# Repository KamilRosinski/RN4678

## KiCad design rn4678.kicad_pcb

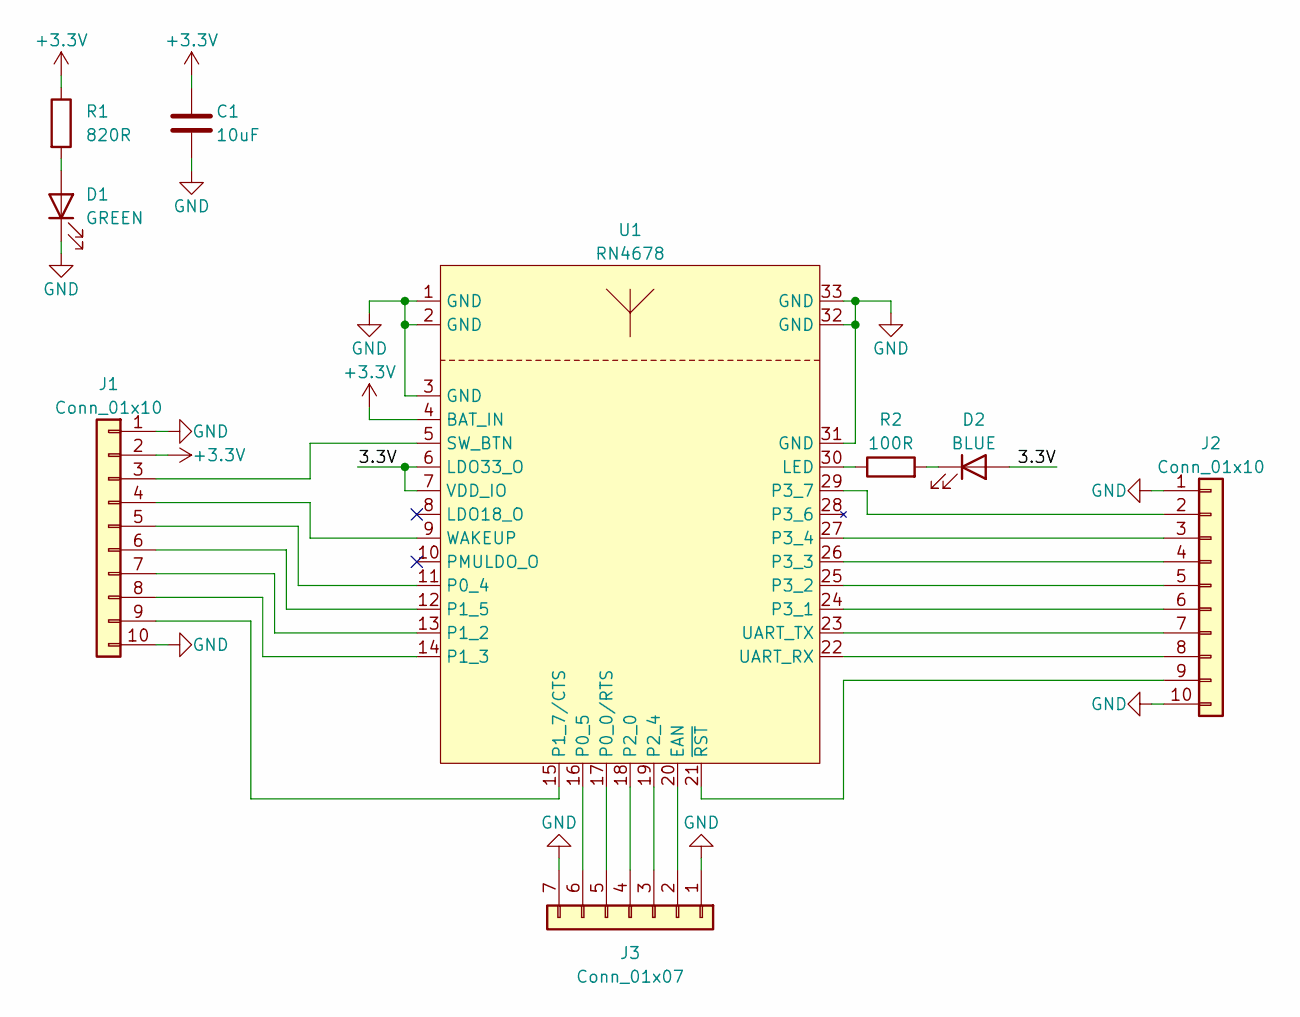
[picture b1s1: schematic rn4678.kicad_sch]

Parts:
C1: 10uF; C_1206_3216Metric
D1: GREEN; LED_0603_1608Metric
D2: BLUE; LED_0603_1608Metric
J1, J2: Conn_01x10; PinHeader_1x10_P2.54mm_Vertical
J3: Conn_01x07; PinHeader_1x07_P2.54mm_Vertical
R1: 820R; R_0603_1608Metric
R2: 100R; R_0603_1608Metric
U1: RN4678

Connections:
+3.3V: C1.1, J1.2, R1.1, U1.4 (BAT_IN)
/3.3V: D2.2 (A), U1.6 (LDO33_O), U1.7 (VDD_IO)
GND: C1.2, D1.1 (K), J1.1, J1.10, J2.1, J2.10, J3.1, J3.7, U1.1 (GND), U1.2 (GND), U1.3 (GND), U1.31 (GND), U1.32 (GND), U1.33 (GND)
unnamed: D1.2 (A), R1.2
unnamed: D2.1 (K), R2.2
unnamed: J1.3, U1.5 (SW_BTN)
unnamed: J1.4, U1.9 (WAKEUP)
unnamed: J1.5, U1.11 (P0_4)
unnamed: J1.6, U1.12 (P1_5)
unnamed: J1.7, U1.13 (P1_2)
unnamed: J1.8, U1.14 (P1_3)
unnamed: J1.9, U1.15 (P1_7/CTS)
unnamed: J2.2, U1.29 (P3_7)
unnamed: J2.3, U1.27 (P3_4)
unnamed: J2.4, U1.26 (P3_3)
unnamed: J2.5, U1.25 (P3_2)
unnamed: J2.6, U1.24 (P3_1)
unnamed: J2.7, U1.23 (UART_TX)
unnamed: J2.8, U1.22 (UART_RX)
unnamed: J2.9, U1.21 (~RST)
unnamed: J3.2, U1.20 (EAN)
unnamed: J3.3, U1.19 (P2_4)
unnamed: J3.4, U1.18 (P2_0)
unnamed: J3.5, U1.17 (P0_0/RTS)
unnamed: J3.6, U1.16 (P0_5)
unnamed: R2.1, U1.30 (LED)

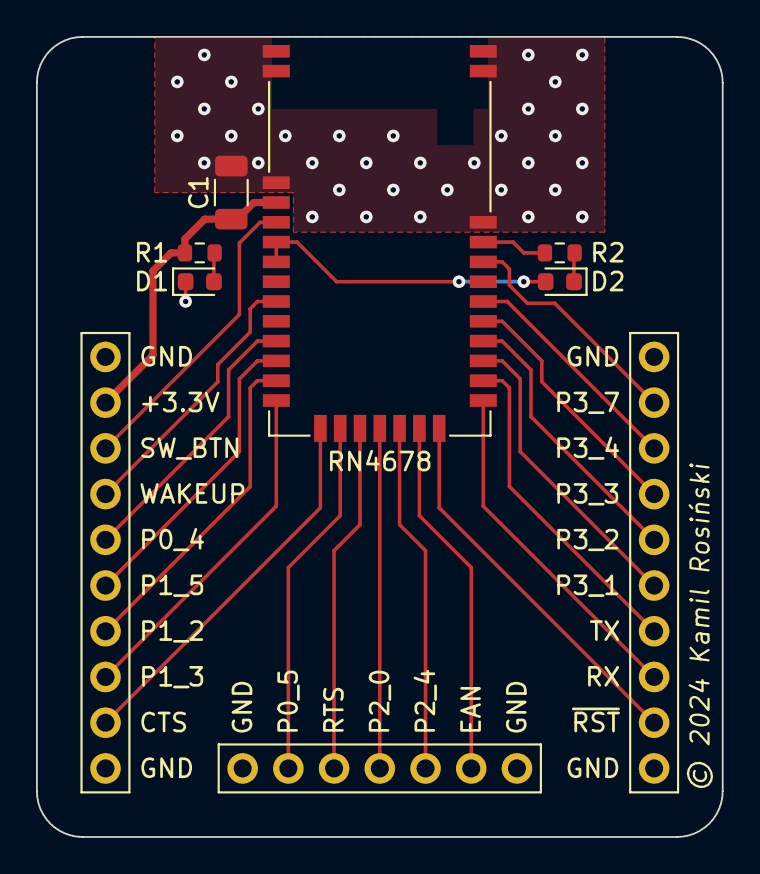
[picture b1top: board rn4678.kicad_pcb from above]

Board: 2 copper layers, 38.1 x 44.4 mm, 9 parts (0 on the bottom side), 26 nets.

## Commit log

2024-03-03 RN4678 breakout board

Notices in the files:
rn4678.kicad_pcb:
© 2024 Kamil Rosiński
